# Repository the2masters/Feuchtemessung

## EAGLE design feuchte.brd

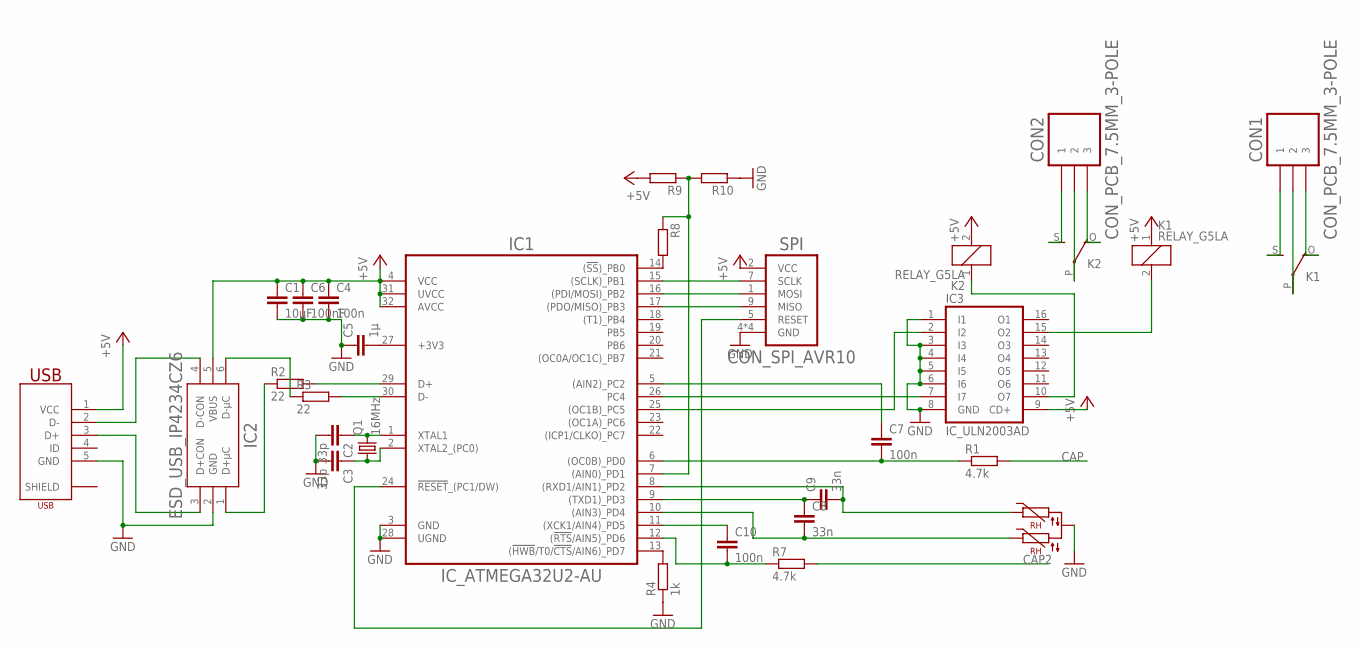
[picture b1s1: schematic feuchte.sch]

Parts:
C1: 10µF; 0603
C2, C3: 33p; 0603
C4, C7, C10: 100n; 0603
C5: 1µ; 0603
C6: 100nF; 0603
C8, C9: 33n; 0603
CON1, CON2: CON_PCB_7.5MM_3-POLE
IC1: IC_ATMEGA32U2-AU
IC2: ESD_USB_IP4234CZ6
IC3: IC_ULN2003AD; SOIC16
K1, K2: RELAY_G5LA
Q1: 16MHz; QUARTZ_HC49S
R1, R7: 4.7k; 0603
R2, R3: 22; 0603
R4: 1k; 0603
R8: RTHT_10MM; R_THT_10MM
R9, R10: RTHT_7.5MM; R_THT_7.5MM
SPI: CON_SPI_AVR10; CON_ISP_AVR10
U$2: SENS_SHS-A5
USB: CON_MICROUSB_ZX62R-B-5P

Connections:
+3V3: C5.2, IC1.27 (+3V3)
+5V: C1.1, C4.1, C6.1, IC1.4 (VCC), IC1.31 (UVCC), IC1.32 (AVCC), IC2.5 (VBUS), IC3.9 (CD+), K1.1, K2.2, R9.2, SPI.2 (VCC), USB.1 (VCC)
CAP: R1.2
CAP2: R7.2
GND: C1.2, C2.2, C3.2, C4.2, C5.1, C6.2, IC1.3 (GND), IC1.28 (UGND), IC2.2 (GND), IC3.1 (I1), IC3.3 (I3), IC3.4 (I4), IC3.5 (I5), IC3.6 (I6), IC3.8 (GND), R4.1, R10.1, SPI.4 (GND), SPI.6 (GND), SPI.8 (GND), SPI.10 (GND), U$2.1, USB.5 (GND)
unnamed: C2.1, IC1.1 (XTAL1), Q1.2
unnamed: C3.1, IC1.2 (XTAL2_(PC0)), Q1.1
unnamed: IC1.15 ((SCLK)_PB1), SPI.7 (SCLK)
unnamed: IC1.16 ((PDI/MOSI)_PB2), SPI.1 (MOSI)
unnamed: IC1.17 ((PDO/MISO)_PB3), SPI.9 (MISO)
unnamed: IC1.24 (!RESET!_(PC1/DW)), SPI.5 (RESET)
unnamed: CON2.2, K2.P
unnamed: C7.1, IC1.5 ((AIN2)_PC2)
unnamed: C7.2, IC1.6 ((OC0B)_PD0), R1.1
unnamed: C10.1, IC1.11 ((XCK1/AIN4)_PD5)
unnamed: IC1.26 (PC4), IC3.7 (I7)
unnamed: IC1.25 ((OC1B)_PC5), IC3.2 (I2)
unnamed: IC3.10 (O7), K2.1
unnamed: IC3.15 (O2), K1.2
unnamed: CON2.1, K2.S
unnamed: CON2.3, K2.O
unnamed: CON1.1, K1.S
unnamed: CON1.2, K1.P
unnamed: CON1.3, K1.O
unnamed: IC1.13 ((!HWB!/T0/!CTS!/AIN6)_PD7), R4.2
unnamed: C9.2, IC1.8 ((RXD1/AIN1)_PD2), U$2.3
unnamed: C8.1, C9.1, IC1.9 ((TXD1)_PD3)
unnamed: C8.2, IC1.10 ((AIN3)_PD4), U$2.2
unnamed: C10.2, IC1.12 ((!RTS!/AIN5)_PD6), R7.1
unnamed: IC1.7 ((AIN0)_PD1), R8.1, R9.1, R10.2
unnamed: IC1.14 ((!SS!)_PB0), R8.2
USBCON_N: IC2.4 (D-CON), USB.2 (D-)
USBCON_P: IC2.3 (D+CON), USB.3 (D+)
USBC_N: IC1.30 (D-), R3.2
USBC_P: IC1.29 (D+), R2.2
USBR_N: IC2.6 (D-µC), R3.1
USBR_P: IC2.1 (D+µC), R2.1

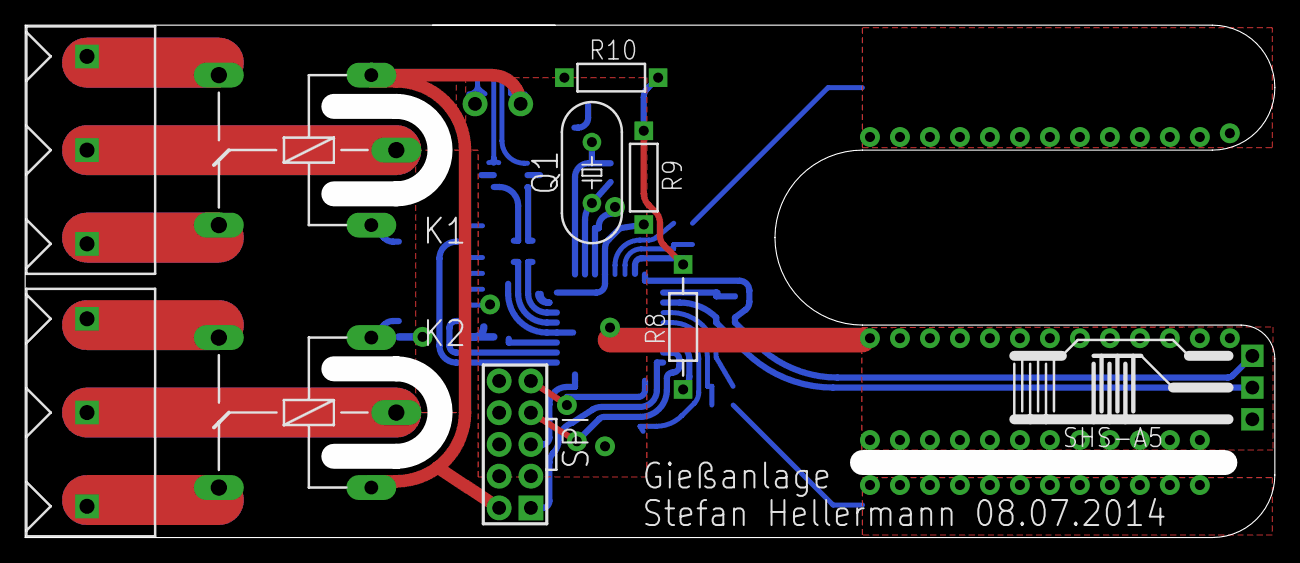
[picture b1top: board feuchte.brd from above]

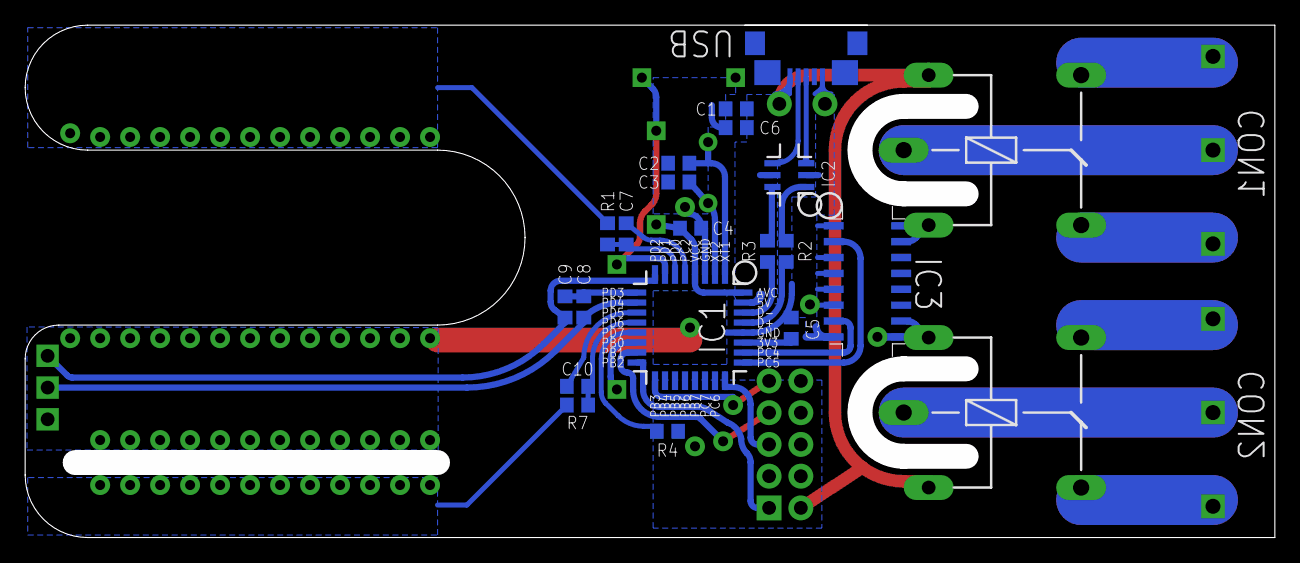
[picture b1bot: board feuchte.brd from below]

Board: 2 copper layers, 100.0 x 41.0 mm, 29 parts (19 on the bottom side), 35 nets.

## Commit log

2014-06-30 Import von ersten Schaltplan und dem Datenblatt vom Atmega32U2
2014-06-30 automatische README löschen
2014-06-30 Bibliothek hinzugefügt
2014-07-01 SMD Bauteile auf Rückseite gespiegelt
2014-07-01 Layer und Beschriftungen in der Bauteilbibliothek optimiert
2014-07-01 Einige DRC fehler aus Bibliothek beseitigt
2014-07-01 ULN2003 aus Eagle verändert um fehler vom DRC zu entfernen und besser dem Datenblatt zu entsprechen
2014-07-01 abends gehts nach hause
2014-07-01 Weiter gelayouted
2014-07-02 Kreise in Packages näher an Bauteil gebracht, um Probleme im Überschneidungen im Layout zu vermeiden
2014-07-03 Quarz HC49S hinzugefügt und weitere kleinere optimierungen
2014-07-03 weiter gelayouted, jetzt mit quarz
2014-07-03 Betauungssensor SHS-A5 hinzugefügt
2014-07-03 2 Kanäle + SHS-A5 im Schaltplan eingefügt
2014-07-05 THT Widerstand hinzugefügt, davon liegen noch genug auf Lager :-)
2014-07-05 ISP Stecker gelayouted, dabei die Relaisversorgung angefasst
2014-07-06 Layout geschätzt bei 80%
2014-07-07 weiter gelayout
2014-07-07 neues dru
2014-07-08 Layout V1 fertig
